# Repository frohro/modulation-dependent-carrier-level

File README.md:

# AWR MDCL Board
The YSE50 Amplitude Modulation Compandor (AMC) board for the ABB (ASEA Brown Bovari) SK-52 transmitters was redesigned  at AWR because we wanted a way to automatically reduce the transmitter power in real-time based on signal-to-noise ratio measurements in the target area.  It also provides us an opportunity to change the modulation-dependent carrier level (MDCL) automatically in real-time, based on the program content and/or the signal-to-noise ratio in the target area.  

This design should work with any transmitter using an ABB PSM (pulse step modulator) for AM or SW broadcasting designed in the 1980s or 1990s. It replaces the YSE 50 or YSE 21 PCBs in the PSM.  I suspect it should work with any transmitter using the YSE 21 or YSE 50.  These boards cost around \\$90,000 around the turn of the century, but you should be able to build this one for about $150 each in 2024, the most expensive parts are the DIN connectors that mate the board to the transmitter.  These boards are far better, because they use software to do the MDCL and facilitate experimentation and optimization.

## MDCL
Adventist World Radio (AWR) on Guam uses modulation-dependent carrier level (MDCL) which is a way of modifying the transmitted AM signal so it uses less power than standard amplitude modulation while hopefully not reducing the listenership.  AM was designed so receivers could be built easily and inexpensively using the technology available in the early 20th century.  A sinusoid at the radio frequency would be modulated (have its amplitude adjusted) as the desired audio signal, $m(t)$, went up and down.  If the radio frequency (RF) sine wave was $A cos(\omega_c t)$ and the audio signal to be transmitted was $m(t)$ where $|m(t)| < 1$, the transmitted signal, $v(t)$ is given by $A(1+m(t))cos(\omega_c t)$. Keeping the magnitude of the audio signal less than one makes $m(t)$ easy to remove from $v(t)$ with an envelope detector enabling very simple receivers to be constructed.  Unfortunately, there is no information in the $1$ term of $(1 + m(t))$, but it does take energy to send it.  If the audio is very soft so that $m(t) << 1$, and the goal is to transmit the information in $m(t)$, it seems especially wasteful.  (Note: Even a public address system playing an analog audio signal like $m(t)$ isn't an equal cost per bit of information.  Loud signals require more power, but they don't always contain more information.  Sometimes the quiet whisper of a friend is worth far more than the loud talk going on.  But for AM modulation the $1$ term has almost nothing to do with the $m(t)$, so it indeed seems a waste to send, at least in a certain sense.)

There are two different types of MDCL, Dynamic Carrier Control (DCC) and Amplitude Modulation Companding (AMC).  

### DCC
DCC reduces the $1$ term in $1 + m(t)$, so less carrier power is transmitted when less is needed, keeping the percentage modulation closer to 100% where the peaks of $m(t) = 1$.   The  DCC signal would be $v_{DCC}(t) = A(k(t)+m(t))cos(\omega_c t)$ .  Because the factor $k < 1$ DCC saves some energy that would have been sent in the carrier perhaps unnecessarily.  It is a slowly varying function of time compared to $m(t)$, so we often think of it as a constant, just $k$. Suppose $k$ was reduced to zero when $m(t) = 0$, then other interfering signals would likely be heard by the receiver instead of silence because most receivers have automatic gain control (AGC) which adjusts the gain up when the signal goes down.  To combat this, $k$ is not usually reduced all the way down to zero.  This leaves a flat carrier for silence, which is usually strong enough that the small noise will be masked out and the receiver will produce silence.

All MDCL schemes use a fast attack slow decay signal based on the absolute value of the modulation signal.  If $m(t)$ quickly gets louder, the changes we make to the RF signal need to respond quickly, but if $m(t)$ decreases in amplitude we should respond slowly to minimize artifacts of our signal processing.  So the first step in doing MDCL is to construct this signal.  We call this signal $m_p(t) = f(|m(t)|)$ where $f$ is the fast attack, slow decay function of time.  In the old analog days, a circuit like this where the capacitor is charged based on the $R_{attack} C$ time-constant and decays based on the $R_{decay} C$ time-constant.  (Rob, replace this figure when you get your tablet-PC going again.)

would have been used.

Below, you can see how $k$ is computed as a function of $m_p(t)$ for DCC.  This function is somewhat heuristic.  The one shown is used in the YSE21 board.  Sometimes $k$ goes back up for low values of $m_p(t)$ to help silence be silent in a real receiver in the presence of interference.

```python
import matplotlib.pyplot as plt
import numpy as np

# Define the x values
x = np.linspace(0, 1, 500)

# Define the y values based on the condition
y = np.piecewise(x, [x < 0.5, x >= 0.5], [0.5, lambda x: (x-0.5)+0.5])

# Create the plot
plt.plot(x, y)

# Label the axes
plt.xlabel('$m_p(t)$')
plt.ylabel('k')

# Set the range for the axes
plt.xlim(0, 1)
plt.ylim(0, 1)

plt.title('DCC Carrier Level, k')

# Display the plot
plt.show()
```

### AMC
AMC takes the view that the soft or silent portions of the broadcast are more important to preserve than the loud portions.  This may be more appropriate for music rather than talk.  It adjusts the amplitude of $v(t)$, instead of just the carrier, as a function of $m_p(t)$ so  $v_{AMC} = A (A_{REL}(1+m(t)))$.  The following graph shows $A_{REL}$ as a function of $m_p(t)$.  Note again, that makes $A_{REL}$ a function of $t$, but since it is relatively slowly varying compared with $m(t)$, so we just call it $A_{REL}$.  

```python
# Define the x values
x = np.linspace(0, 1, 500)

# Define the y values based on the condition
y = np.piecewise(x, [x < 0.1, x >= 0.1], [1, lambda x: (-0.5/.9*x+1+.1*.5/.9)])

# Create the plot
plt.plot(x, y)

# Label the axes
plt.xlabel('$m_p(t)$')
plt.ylabel('$A_{REL}$')

# Set the range for the axes
plt.xlim(0, 1)
plt.ylim(0, 1.1)

plt.title('AMC Relative Signal Level, $A_{REL}$')

# Display the plot
plt.show()
```

AMC peak output power of the transmitter is the same as the output from the carrier alone.  For example, an SK-52 transmitter with a normal AM power level specified at 100 kW, means the carrier alone will output 100 kW average power.  On peak modulation, the output will be 400 kW because the $m(t)$ adds to the $1$ to become $2$ for 100% modulation at peaks of $m(t)$ giving $4$ times the power because power is proportional to the square of the voltage which is twice what it was for the carrier alone.  AMC thus saves power and wear and tear on the transmitter, by reducing the average power it is transmitting under larger modulation.  

There are variations on these two themes of MDCL one can dream about.  It is claimed that AMC is better for music, while DCC is better for speech.  AMC is more popular with medium wave AM stations.  It may sound better at least to some.  DCC only reduces carrier power, and that really doesn't contain any information other than silence.  Previous experiments with DCC indicated it actually sounds louder to the listener due to the way the receiver AGC and the transmitter DCC interact which is good for short wave.  AMC will save the station more money than DCC, but so would simply turning the power down.  Turning the power down is the major improvement we wish to add to the options, so we can use AMC, DCC, or ordinary AM, but only the power needed.  In the past it was not easy to measure how much power was needed, but now with Internet connected receivers, it can be done fairly easily.  Since the space weather changes the signal levels for skywave signals, this will change over time, so there will be times when less power is needed than the maximum possible.  In general a cut in power by half is only barely perceptible to the listener, so significant savings on the power bill can be expected.  The plan is to measure the signal-to-noise ratio every 15 minutes or so and change the transmitter power as appropriate.

## Transmitter Operation
AWR Guam has five ABB SK-52 100 kW transmitters.  They use the standard modulation method, where the B+ high voltage on the plate of the final amplifiers is supplied by the modulator, which produces an amplified version of the output of the MDCL output signal.  By varying this voltage on the plate of the final RF amplifier, the output signal’s amplitude is set.  This is called modulating the transmitter.   See the diagram below.

A Pulse Step Modulator (PSM) is used to create the “Audio + DC Carrier Voltage” in the diagram above.  The PSM is essentially like a digital to analog converter where 26 voltage sources are switched in series by digital signals.  It is like a 26 level digital to analog converter with an output of 22 kV maximum.  When the AM transmitter (no MDCL) is sending silence, the PSM puts out 11 kV.  At 100% modulation where the $max (|m(t)|) = 1$, it puts out between 0 and 22 kV as the audio, $m(t)$ goes up and down.  Below is a basic diagram of a PSM.  The switches are controlled digitally and in the SK-52 are gate turn off (GTO) devices.  The blue, green, magenta and orange circular symbols are voltage sources.  (Rob, to avoid copyright, we could replace these when you have your bricked computer back.)

The most obvious place in the circuit to incorporate a modification to the SK-52 transmitters is in the MDCL board, so YS50 was replaced.  The MDCL board is where something can be incorporated into the circuit to lower the power when a remote Internet connected receiver in the target area indicates the transmitter could cut power without significantly lowering the number of listeners.  We just add one more parameter we can control that multiplies whatever type of audio signal we have by a slowly varying "constant", that changes perhaps every 15 minutes as the signal-to-noise ratio is updated.  If this constant is called $A_{att}$, it would have a maximum value of $1$ for maximum power, and $0.707$ for half power, or $0.5$ for quarter power.  

Note in the blue AM Transmitter Block Diagram above, the screen grid in the vacuum tube.  Unless the voltage on the screen is also controlled by the MDCL board, a risk exists that the screen current will increase beyond acceptable limits.  For example if the plate of the tube is at $0$ volts, and the screen at a higher voltage, the screen will act as the plate normally would and the screen current would be way to high.  This means there is a limit to how much we can drop $A_{att}$.  A solution to this problem is to increase the resistor between the screen supply and the screen.  We were able to drop the power to 25% of maximum.  (Rob, make sure this is correct.)

We also noted a problem with the PSM protection circuitry which styll needs to be ironed out.

The transmitter has a limit to how long the modulation, $m(t)$ can exceed a certain value, so that the transmitter is not operated beyond 100 kW for longer than is good for it.  This limit is enforced in the MDCL software as well.

## Board Description

### Hardware
The hardware is based on a [PJRC Teensy 4.1 development board](https://www.pjrc.com/store/teensy41.html).  It features a 600 MHz ARM Cortex-M7 processor with FPU, nice Arduino DSP library, a USB 2.0 port and Ethernet.  The data $1+m(t)$ comes in as a 5V TTL digital 12-bit parallel signal sampled at 100 kHz.  This signal is converted to a serial signal by a pair of 74LV165 parallel to serial conversion ICs.  These also convert the 5V TTL level signals of the input data to 3.3 V logic levels.  This serial data is read into the Teensy using SPI0.  The Teensy processes the signal as needed and sends the data to a serial to parallel conversion performed by a pair of 74ACHT595 ICs, which send the result on to the next board in the transmitter.  There is a CH340G that allows use of a second USB serial port for debugging (Serial2 for the Arduino) and four connectors for the inexpensive eight bit logic analyzers from China to read the serial and parallel data.  There are a number of LEDs for indicators and debugging and some provision for connecting other signals to the Teensy in case we overlooked something.  The Teensy we are using comes with Ethernet, and we send the real-time control signals over that medium.

The Teensy has a feature that may eventually be used to eliminate the analog stages of the whole broadcast system, making the whole system at KSDA digital, from the digital audio in all the way to the PSM of the transmitter.  This feature is the USB connector on the Teensy can be made to look just like a USB sound card for a computer operating at the 44.1 kHz sample rate. I have tested the Linux sample rate conversion library runing a sinc interpolator and it looks feasible to convert from 44.1 kHz to 100 kHz in real time, leaving about half the time between 100 kHz samples for DSP.  Optical USB extenders can be used to span the distance between the transmitters and the audio distribution computer.

### Software

#### Toolchain
You can build this with the Arduino IDE using Teensyduino or with VScode.  The latter gives you a nicer environment, but the former is quicker to set up.

#### Serial Input
The SPI (SPI0) is used for the serial data transfer of the input data.  The upper four bits of the 16 bit word should be zero.  If not, you have RFI or something bad happening.  The Teensy 4.1 supports a depreciated legacy way or doing the transactions, but also has the new recommend way.  Using that method, the speed can be increased from 12 MHz to 80 MHz.  The setup function shows how to set things up, and the ISR is shown below:
// ISR function called by the interrupt that is triggered by L1
// to process the new word from the transmitter
void receive2ByteWord() // Receive 16-bit word from SPI0
{                       // Select the slave device
  SPI.beginTransaction(spiSettings);
  digitalWrite(chipSelectPin0, LOW);
  // Send a dummy byte to initiate the SPI read and receive the 16-bit word
  uint16_t dummy = 0x00;
  receivedWord = SPI.transfer16(dummy); // Deselect the slave device
  digitalWrite(chipSelectPin0, HIGH);
  validWord = 1; // Indicates that the new 16-bit word is received and ready to process
  SPI.endTransaction();
}
#### Serial Output
The SPI1 bus is used for transferring data to the serial to parallel converter so the data will be ready for a parallel read by the transmitter.  Like the serial input, the setup function gets the SPI initialized and the following code is the ISR that happens when triggered by LC.
// ISR function called by the interrupt that is triggered by L5 to send the
// processed word to the transmitter (DCC board used LC, but L5 is faster)
void send2ByteWord()
{
  SPI1.beginTransaction(spiSettings);

  digitalWrite(chipSelectPin1, LOW); //  We are not using CS1.
  SPI1.transfer16(wordToSend);       // Send the 16-bit word to the transmitter
  digitalWrite(chipSelectPin1, HIGH);
  SPI1.endTransaction();
}
DCC and MDCL Processing
uint16_t processMDCL(uint16_t one_plus_m_t)
// See the MDCL.ipynb for the theory on this.
{ // This function takes a 16-bit word whose lower 12 bits is 1+m(t) and processes it according to the MDCL algorithm
  // We could put a check for overmodulation here if wanted (Check for repeated 0's)
  if (digitalRead(SSBOnOffPin) == LOW && digitalRead(NFBereitPin) == HIGH && digitalRead(DCCOnOffPin) == HIGH)
  { // if MCDL is on
    uint16_t m_p;
    static uint16_t m_pPrevious = 0;     // store the previous m_p(t) value
    static uint16_t samplesUntilDecay = samplesPerDecay; // This is the number of samples until the decay starts

    if (one_plus_m_t < 2048)           // Find |m(t)| value where 1 + m(t) scaled to 0 to 4095
    {
      m_p = 2048 - one_plus_m_t; // This should not overflow.
    }
    else
    {
      m_p = one_plus_m_t - 2048; // This should not overflow.
    }
    #ifdef DEBUG
    uint16_t m_p_a;
    m_p_a = m_p;  // mpa is for debugging.  It is m_p without the decay.
    #endif
    // m_p(t) needs to be a fast attack, slow decay function of time
    if (m_p <= m_pPrevious) // m_p is decreasing
    { 
      m_p = m_pPrevious; // m_p(t) should not decrease
      if (samplesUntilDecay > 0) // Will decay down to close to 0 (within samplesPerDecay) if m_p(t) is not increasing
      {
        samplesUntilDecay--;
      }
      else // sammples until decay is 0, so decay one step
      {
        if (m_p > 0) m_p--; // m_p should not be decreased below zero
        samplesUntilDecay = samplesPerDecay; // Reset the decay counter
      }
    }
    else // m_p in increasing so don't decay m_p(t).  It needs to rise instantly, but samplesPerDecay needs to be reset so it is ready for the next decay.
    {
      samplesUntilDecay = samplesPerDecay; // Reset the decay counter
    }
    m_pPrevious = m_p; // Store the current m_p(t) value for the next cycle
    if (currentMDCLNumber == 0) // DCC
    {
      if (digitalRead(DCCPin) != HIGH) // Change indicator LEDs if needed
      {
        digitalWrite(DCCPin, HIGH);
        digitalWrite(AMCPin, LOW);
      }
      uint16_t dccK; // See the graph of DCC k as a function of m_p(t).  We may want to pass the 430 and 1024 parameters in someday
      if (m_p > 1024)
      {
        dccK = m_p;
      }
      else if (m_p < 430) // Using curve as used for ABB high power transmitters (> 100 kW)
      {
        dccK = 1454 - m_p;  // 1454 = 1024 + 430
      }
      else
      {
        dccK = 1024;
      }
      return percentAdjust * ((dccK + one_plus_m_t)-2048); // percentAdjust is to turn the power down
    }
    else if (currentMDCLNumber == 1) // AMC
    {
      if (digitalRead(AMCPin) != HIGH) // Change the indicator LEDs if needed
      {
        digitalWrite(DCCPin, LOW);
        digitalWrite(AMCPin, HIGH);
      }
      {
        digitalWrite(DCCPin, LOW);
        digitalWrite(AMCPin, HIGH);
      }
      float AMC_REL = (2048 - m_p / 2)/2048.0;                        // This should not overflow.
      return percentAdjust * ((AMC_REL * one_plus_m_t)); // percentAdjust < 1, is to turn the power down
    }
  }
  return percentAdjust * one_plus_m_t; // If MDCL is off, just pass the word through adjusted for desired power output
}

#### Keeping from Damaging the Transmitter by Asking for Too Much Power
The PSM manual description of YSE27 (pages 42-44) describe how long a signal that would transmit more than 100 kW is allowed.  You cannot have more than 2500 for longer than 10 mS.  If it happens, then you need to drop to the carrier level (2048) until the signal goes below the carrier level.  At first I was unable to determine if YSE27 was before or after YSE21 (the DCC unit we are replacing) so we wrote a safety routine that kept the MDCL board from violating the conditions needed for a healthy transmitter described there.  There were still possibilities of a bug that this would not catch, so I went back and finally found that YSE21 is before YSE27 in the transmitter.  It makes more sense to put this check at the end of the line, not in the DCC section, so our code was redundant, and was a possible place for bugs.  The block diagram in section 5 of Volume 7 Schematic Diagrams AF Stages (PSM), YSE-27 documents this.  I am removing our redundant code to make the software simpler.  (Rob 9/2/24).  This relieves a fear that we could ask the transmitter for more power than it could handle and it would burn up.

#### Screen Modifications
The final tube screen voltage gets more and more attractive for electrons relative to the plate (anode) so an extra screen resistor was added to the screen power supply and possibly the voltage tap will be changed to reduce the screen voltage.

### Things Tested and Look Good
* SPI at 80 MHz both in and out good!
    * No data outside the 12 bit range like Ray had with the slower SPI
* Timing of SPI (input and output)
* Main loop usually happens every uS, but every 4th time it is 3.5 uS
* processMDCL with dontBurnTransmitterUP uses 300 nS (0.3 uS)  (fast enough)
* MDCL works (tested using triangle under all conditions)
* Make sure if loop() is delayed, it just keeps sending out the same wordToSend.  This will cover short timing problems, where loop() gets delayed.  It does.  
* Watch out for RFI!
### Things to test
* Different MDCL types and power levels while listening to remote receivers
* Lower voltage taps on screen power supply
### Things to Improve
* The messages in TCP/IP communication are too long.
* The code quoted in this keeps improving, making this difficult to keep up to date.  We need a better way of documenting it.
### Priorities for Rob before leaving Guam in order of Priority
* Get the MDCL board running smoothly.  Hopefully we can be running it in one of the transmitters full time by the time I leave.
    * Investigate how different MDCL methods and power levels are seen from remote receivers.
    * Documentation for the MDCL board and videos
* Finish getting the PostgreSQL database going for automated monitoring.
* Get the automated power level software going.

## Operation
#### RFI
Beware of RFI.  The PSM in the transmitter gets ">OFF" errors (meaning it is taking too long to turn off PSM modules, which is bad because the switch (GTO) dissipates power whenever it is turning on or off and the energy dissipated depends on how quickly you switch).  These appear to be caused by RF feedback into the system through the MDCL board when it is on the extender board for testing.  So only test it with it inside the transmitter case if the test involves transmitting, and do not leave any cables connected to it because they act as antennas.  If cables must be connected, use ferrite torroids to suppress common mode RF and optical fiber instead of copper wires wherever possible.

Compute what the minimum power output will be with your MDCL and make sure it does not go below 10 kW.  We could put a test in the code to not send something below 648.

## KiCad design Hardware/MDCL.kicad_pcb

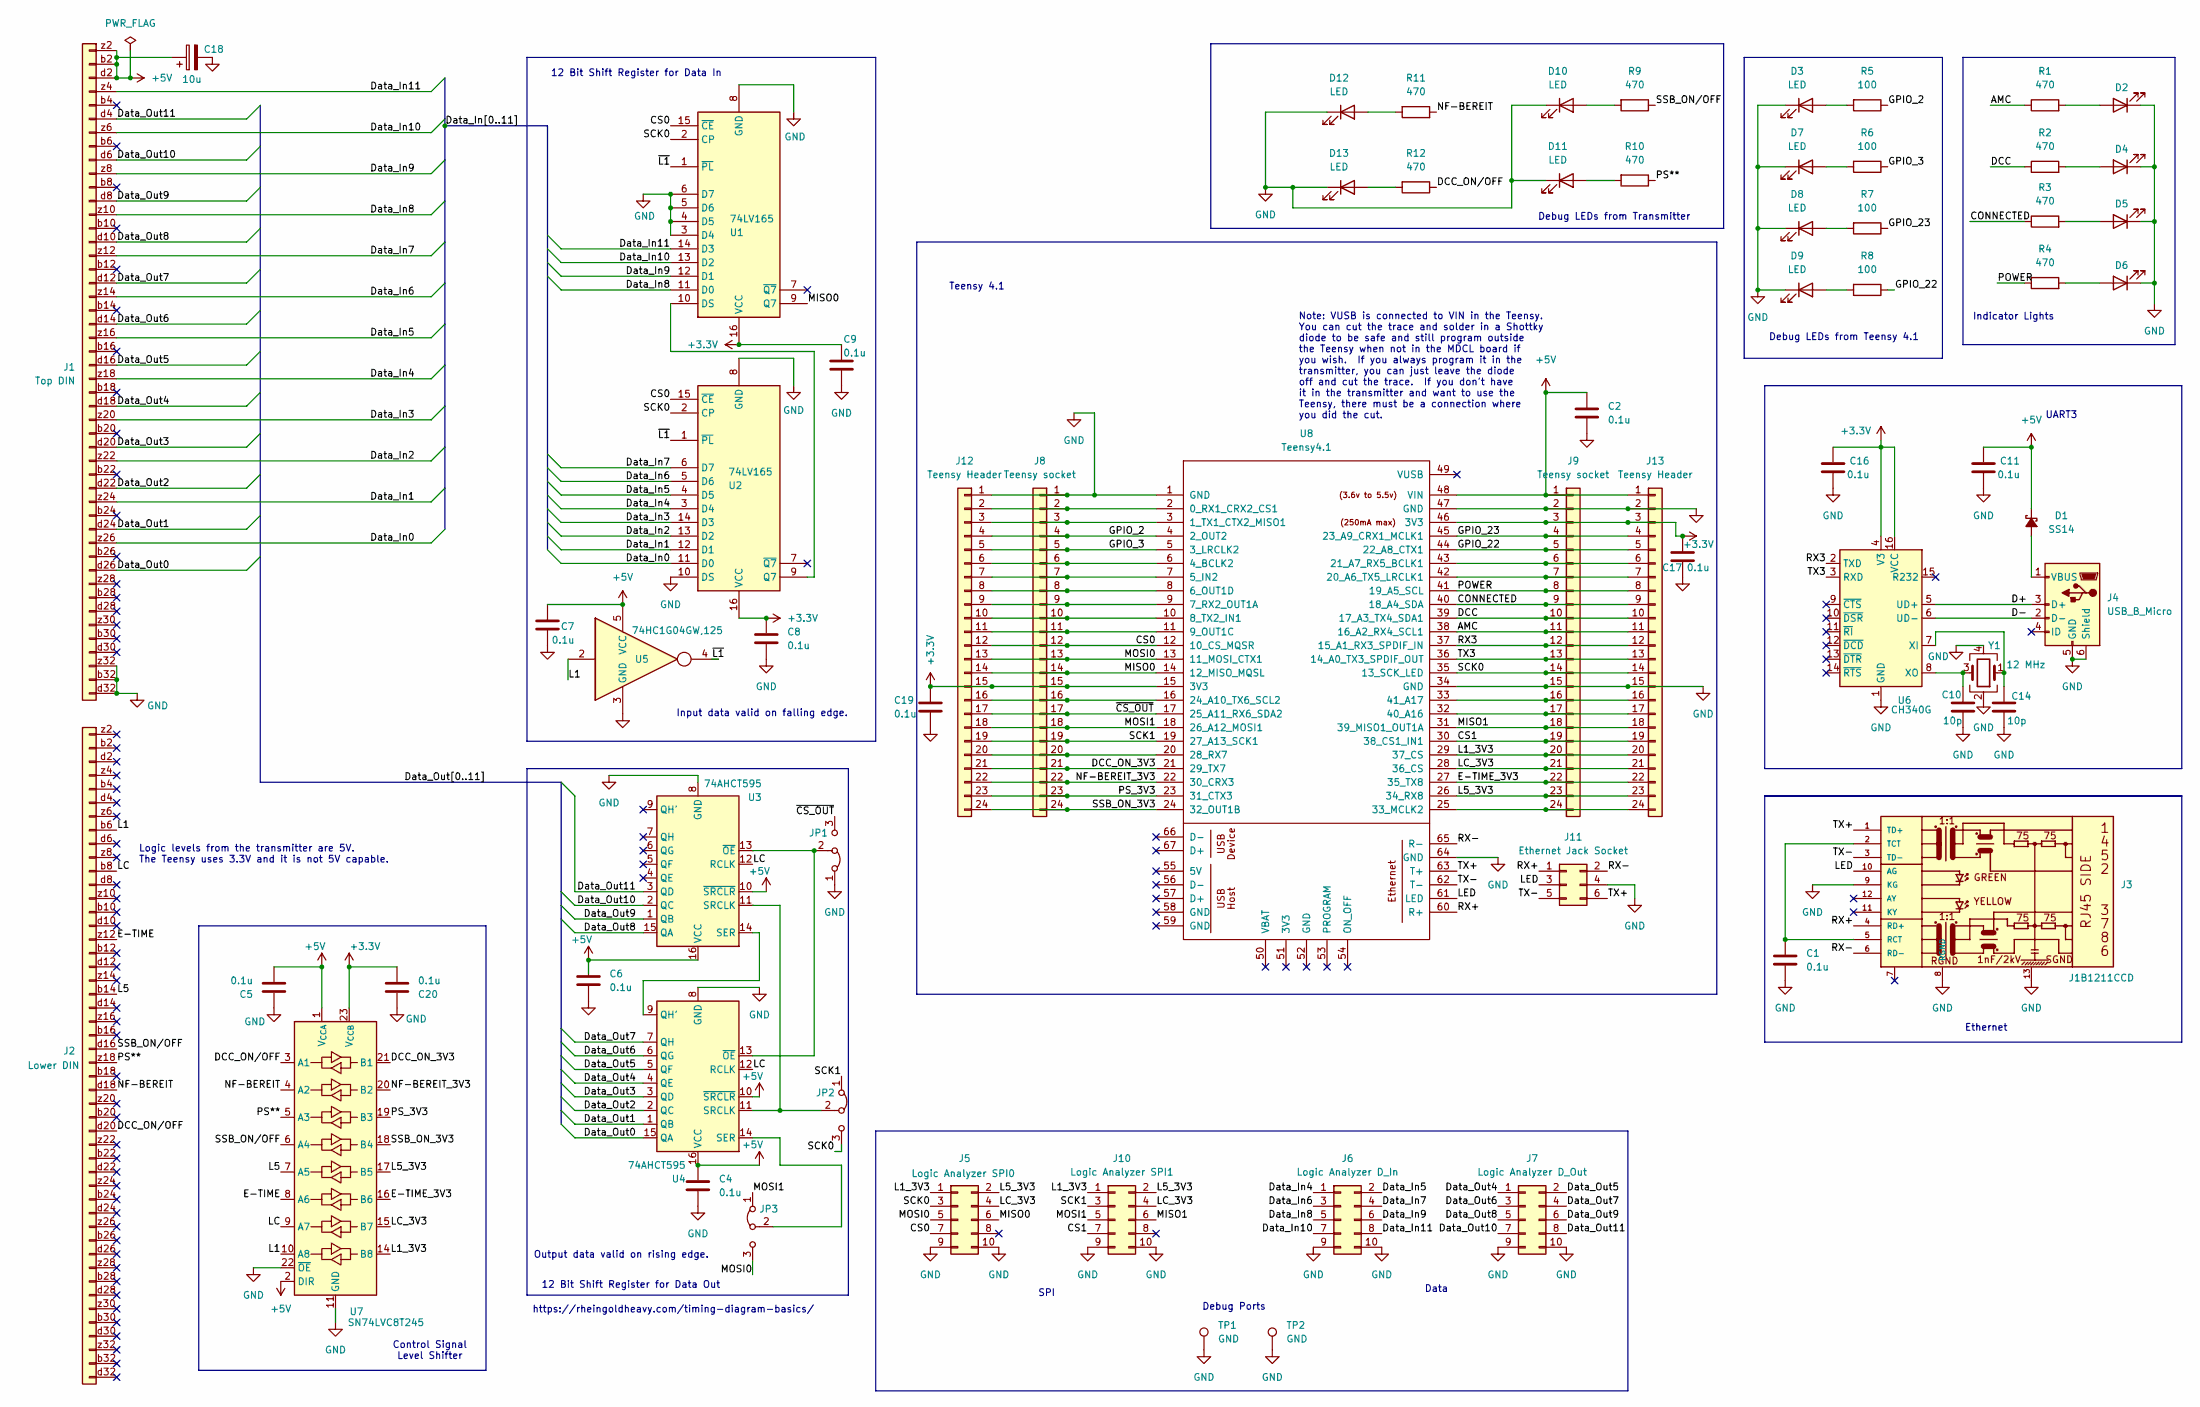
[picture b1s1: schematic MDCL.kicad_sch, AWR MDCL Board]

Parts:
C1, C2, C4, C5, C6, C7, C8, C9, C11, C16, C17, C19, C20: 0.1u; C_0805_2012Metric; LCSC C49678
C10, C14: 10p; C_0603_1608Metric; LCSC C1634
C18: 10u; C_0805_2012Metric; LCSC C15850
D1: SS14; D_SMA; LCSC C2480
D2, D4, D5, D6: HV-32H307B/260/XSYG; LED_3.0mm_2.54mm_lead_spacing_horizontal
D3, D7, D8, D9, D10, D11, D12, D13: LED; LED_0603_1608Metric; LCSC C2290
J1: Top DIN; DIN41612_F_3x16_Male_Horizontal_THT
J2: Lower DIN; DIN41612_F_3x16_Male_Horizontal_THT
J3: J1B1211CCD; RJ45_Cetus_J1B1211CCD_Horizontal; LCSC C910371
J4: USB_B_Micro; USB_Micro-Yuandi-G3P3-A1T2; LCSC C2682512
J5: Logic Analyzer SPI0; IDC-Header_2x05_P2.54mm_Vertical_SMD; LCSC C2843214
J6: Logic Analyzer D_In; IDC-Header_2x05_P2.54mm_Vertical_SMD; LCSC C2843214
J7: Logic Analyzer D_Out; IDC-Header_2x05_P2.54mm_Vertical_SMD; LCSC C2843214
J8, J9: Teensy socket; PinHeader_1x24_P2.54mm_Vertical; LCSC C7506622
J10: Logic Analyzer SPI1; IDC-Header_2x05_P2.54mm_Vertical_SMD; LCSC C2843214
J11: Ethernet Jack Socket; PinHeader_2x03_P2.00mm_Vertical_SMD; LCSC C3975167
J12, J13: Teensy Header; PinHeader_1x24_P2.54mm_Vertical
JP1, JP2, JP3: Jumper_3_Bridged12; SolderJumper-3_P1.3mm_Bridged12_RoundedPad1.0x1.5mm_NumberL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
R1, R2, R3, R4: 470; R_1206_3216Metric; LCSC C17936
R5, R6, R7, R8: 100; R_0805_2012Metric; LCSC C17408
R9, R10, R11, R12: 470; R_0603_1608Metric; LCSC C23179
TP1, TP2: GND; TestPoint_THTPad_4.0x4.0mm_Drill2.0mm
U1, U2: 74LV165; TSSOP-16_4.4x5mm_P0.65mm; LCSC C201716
U3, U4: 74AHCT595; TSSOP-16_4.4x5mm_P0.65mm; LCSC C554707
U5: 74HC1G04GW,125; SOT-353_SC-70-5; LCSC C10234
U6: CH340G; SOP-16_3.9x9.9mm_P1.27mm; LCSC C14267
U7: SN74LVC8T245; TSSOP-24_4.4x7.8mm_P0.65mm; LCSC C7859
U8: Teensy4.1
Y1: 12 MHz; Crystal_SMD_2520-4Pin_2.5x2.0mm; LCSC C963522

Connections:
+3.3V: C8.1, C9.1, C16.1, C17.1, C19.1, C20.2, J8.15, J9.3, J12.15, J13.3, U1.16 (VCC), U2.16 (VCC), U6.4 (V3), U6.16 (VCC), U7.23 (V_{CCB}), U7.24 (V_{CCB}), U8.15 (3V3), U8.46 (3V3)
+5V: C2.1, C4.1, C5.2, C6.1, C7.1, C11.1, C18.1, D1.1 (K), J1.b2, J1.d2, J1.z2, J9.1, J13.1, U3.10 (~SRCLR), U3.16 (VCC), U4.10 (~SRCLR), U4.16 (VCC), U5.5 (VCC), U7.1 (V_{CCA}), U7.2 (DIR), U8.48 (VIN)
/AMC: J9.11, J13.11, R1.1, U8.38 (16_A2_RX4_SCL1)
/CONNECTED: J9.9, J13.9, R3.1, U8.40 (18_A4_SDA)
/CS0: J5.7, J8.12, J12.12, U1.15 (~CE), U2.15 (~CE), U8.12 (10_CS_MQSR)
/CS1: J9.19, J10.7, J13.19, U8.30 (38_CS1_IN1)
/D+: J4.3 (D+), U6.5 (UD+)
/D-: J4.2 (D-), U6.6 (UD-)
/DCC: J9.10, J13.10, R2.1, U8.39 (17_A3_TX4_SDA1)
/DCC_ON_3V3: J8.21, J12.21, U7.21 (B1), U8.21 (29_TX7)
/DCC_ON/OFF: J2.d20, R12.1, U7.3 (A1)
/Data_In0: J1.z26, U2.11 (D0)
/Data_In1: J1.z24, U2.12 (D1)
/Data_In2: J1.z22, U2.13 (D2)
/Data_In3: J1.z20, U2.14 (D3)
/Data_In4: J1.z18, J6.1, U2.3 (D4)
/Data_In5: J1.z16, J6.2, U2.4 (D5)
/Data_In6: J1.z14, J6.3, U2.5 (D6)
/Data_In7: J1.z12, J6.4, U2.6 (D7)
/Data_In8: J1.z10, J6.5, U1.11 (D0)
/Data_In9: J1.z8, J6.6, U1.12 (D1)
/Data_In10: J1.z6, J6.7, U1.13 (D2)
/Data_In11: J1.z4, J6.8, U1.14 (D3)
/Data_Out0: J1.d26, U4.15 (QA)
/Data_Out1: J1.d24, U4.1 (QB)
/Data_Out2: J1.d22, U4.2 (QC)
/Data_Out3: J1.d20, U4.3 (QD)
/Data_Out4: J1.d18, J7.1, U4.4 (QE)
/Data_Out5: J1.d16, J7.2, U4.5 (QF)
/Data_Out6: J1.d14, J7.3, U4.6 (QG)
/Data_Out7: J1.d12, J7.4, U4.7 (QH)
/Data_Out8: J1.d10, J7.5, U3.15 (QA)
/Data_Out9: J1.d8, J7.6, U3.1 (QB)
/Data_Out10: J1.d6, J7.7, U3.2 (QC)
/Data_Out11: J1.d4, J7.8, U3.3 (QD)
/E-TIME: J2.z12, U7.8 (A6)
/E-TIME_3V3: J9.22, J13.22, U7.16 (B6), U8.27 (35_TX8)
/GPIO_2: J8.4, J12.4, R5.1, U8.4 (2_OUT2)
/GPIO_3: J8.5, J12.5, R6.1, U8.5 (3_LRCLK2)
/GPIO_22: J9.5, J13.5, R8.1, U8.44 (22_A8_CTX1)
/GPIO_23: J9.4, J13.4, R7.1, U8.45 (23_A9_CRX1_MCLK1)
/L1: J2.b6, U5.2, U7.10 (A8)
/L1_3V3: J5.1, J9.20, J10.1, J13.20, U7.14 (B8), U8.29 (37_CS)
/L5: J2.b14, U7.7 (A5)
/L5_3V3: J5.2, J9.23, J10.2, J13.23, U7.17 (B5), U8.26 (34_RX8)
/LC: J2.b8, U3.12 (RCLK), U4.12 (RCLK), U7.9 (A7)
/LC_3V3: J5.4, J9.21, J10.4, J13.21, U7.15 (B7), U8.28 (36_CS)
/LED: J3.10 (AG), J11.3, U8.61 (LED)
/MISO0: J5.6, J8.14, J12.14, U1.9 (Q7), U8.14 (12_MISO_MQSL)
/MISO1: J9.18, J10.6, J13.18, U8.31 (39_MISO1_OUT1A)
/MOSI0: J5.5, J8.13, J12.13, JP3.3 (B), U8.13 (11_MOSI_CTX1)
/MOSI1: J8.18, J10.5, J12.18, JP3.1 (A), U8.18 (26_A12_MOSI1)
/NF-BEREIT: J2.d18, R11.1, U7.4 (A2)
/NF-BEREIT_3V3: J8.22, J12.22, U7.20 (B2), U8.22 (30_CRX3)
/POWER: J9.8, J13.8, R4.1, U8.41 (19_A5_SCL)
/PS**: J2.z18, R10.1, U7.5 (A3)
/PS_3V3: J8.23, J12.23, U7.19 (B3), U8.23 (31_CTX3)
/RX3: J9.12, J13.12, U6.2 (TXD), U8.37 (15_A1_RX3_SPDIF_IN)
/RX+: J3.4 (RD+), J11.1, U8.60 (R+)
/RX-: J3.6 (RD-), J11.2, U8.65 (R-)
/SCK0: J5.3, J9.14, J13.14, JP2.3 (B), U1.2 (CP), U2.2 (CP), U8.35 (13_SCK_LED)
/SCK1: J8.19, J10.3, J12.19, JP2.1 (A), U8.19 (27_A13_SCK1)
/SSB_ON_3V3: J8.24, J12.24, U7.18 (B4), U8.24 (32_OUT1B)
/SSB_ON/OFF: J2.d16, R9.1, U7.6 (A4)
/TX3: J9.13, J13.13, U6.3 (RXD), U8.36 (14_A0_TX3_SPDIF_OUT)
/TX+: J3.1 (TD+), J11.6, U8.63 (T+)
/TX-: J3.3 (TD-), J11.5, U8.62 (T-)
/~CS_OUT: J8.17, J12.17, JP1.3 (B), U8.17 (25_A11_RX6_SDA2)
/~L1: U1.1 (~PL), U2.1 (~PL), U5.4
GND: C1.2, C2.2, C4.2, C5.1, C6.2, C7.2, C8.2, C9.2, C10.2, C11.2, C14.2, C16.2, C17.2, C18.2, C19.2, C20.1, D2.2 (K), D3.1 (K), D4.2 (K), D5.2 (K), D6.2 (K), D7.1 (K), D8.1 (K), D9.1 (K), D10.1 (K), D11.1 (K), D12.1 (K), D13.1 (K), J1.b32, J1.d32, J1.z32, J3.8 (RGND), J3.9 (KG), J3.13, J4.5 (GND), J4.6 (Shield), J5.9, J5.10, J6.9, J6.10, J7.9, J7.10, J8.1, J9.2, J9.15, J10.9, J10.10, J11.4, J12.1, J13.2, J13.15, JP1.1 (A), TP1.1, TP2.1, U1.3 (D4), U1.4 (D5), U1.5 (D6), U1.6 (D7), U1.8 (GND), U2.8 (GND), U2.10 (DS), U3.8 (GND), U4.8 (GND), U5.3 (GND), U6.1 (GND), U7.11 (GND), U7.12 (GND), U7.13 (GND), U7.22 (~OE), U8.1 (GND), U8.34 (GND), U8.47 (GND), U8.64 (GND), Y1.2, Y1.4
unnamed: D1.2 (A), J4.1 (VBUS)
unnamed: D2.1 (A), R1.2
unnamed: D3.2 (A), R5.2
unnamed: D4.1 (A), R2.2
unnamed: D5.1 (A), R3.2
unnamed: D6.1 (A), R4.2
unnamed: D7.2 (A), R6.2
unnamed: D8.2 (A), R7.2
unnamed: D9.2 (A), R8.2
unnamed: D10.2 (A), R9.2
unnamed: D11.2 (A), R10.2
unnamed: D12.2 (A), R11.2
unnamed: D13.2 (A), R12.2
unnamed: C1.1, J3.2 (TCT), J3.5 (RCT)
unnamed: J8.2, J12.2, U8.2 (0_RX1_CRX2_CS1)
unnamed: J8.3, J12.3, U8.3 (1_TX1_CTX2_MISO1)
unnamed: J8.6, J12.6, U8.6 (4_BCLK2)
unnamed: J8.7, J12.7, U8.7 (5_IN2)
unnamed: J8.8, J12.8, U8.8 (6_OUT1D)
unnamed: J8.9, J12.9, U8.9 (7_RX2_OUT1A)
unnamed: J8.10, J12.10, U8.10 (8_TX2_IN1)
unnamed: J8.11, J12.11, U8.11 (9_OUT1C)
unnamed: J8.16, J12.16, U8.16 (24_A10_TX6_SCL2)
unnamed: J8.20, J12.20, U8.20 (28_RX7)
unnamed: J9.6, J13.6, U8.43 (21_A7_RX5_BCLK1)
unnamed: J9.7, J13.7, U8.42 (20_A6_TX5_LRCLK1)
unnamed: J9.16, J13.16, U8.33 (41_A17)
unnamed: J9.17, J13.17, U8.32 (40_A16)
unnamed: J9.24, J13.24, U8.25 (33_MCLK2)
unnamed: JP1.2 (C), U3.13 (~OE), U4.13 (~OE)
unnamed: JP2.2 (C), U3.11 (SRCLK), U4.11 (SRCLK)
unnamed: JP3.2 (C), U4.14 (SER)
unnamed: U1.10 (DS), U2.9 (Q7)
unnamed: U3.14 (SER), U4.9 (QH')
unnamed: C14.1, U6.7 (XI), Y1.1
unnamed: C10.1, U6.8 (XO), Y1.3

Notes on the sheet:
Debug Ports
12 Bit Shift Register for Data In
Input data valid on falling edge.
https://rheingoldheavy.com/timing-diagram-basics/
Control Signal Level Shifter
UART3
Indicator Lights
Debug LEDs from Transmitter
Logic levels from the transmitter are 5V. The Teensy uses 3.3V and it is not 5V capable.
Ethernet
Data
Output data valid on rising edge.
12 Bit Shift Register for Data Out
Note: VUSB is connected to VIN in the Teensy. You can cut the trace and solder in a Shottky diode to be safe and still program outside the Teensy when not in the MDCL board if you wish. If you always program it in the transmitter, you can just leave the diode off and cut the trace. If you don't hav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
Teensy 4.1
SPI
Debug LEDs from Teensy 4.1

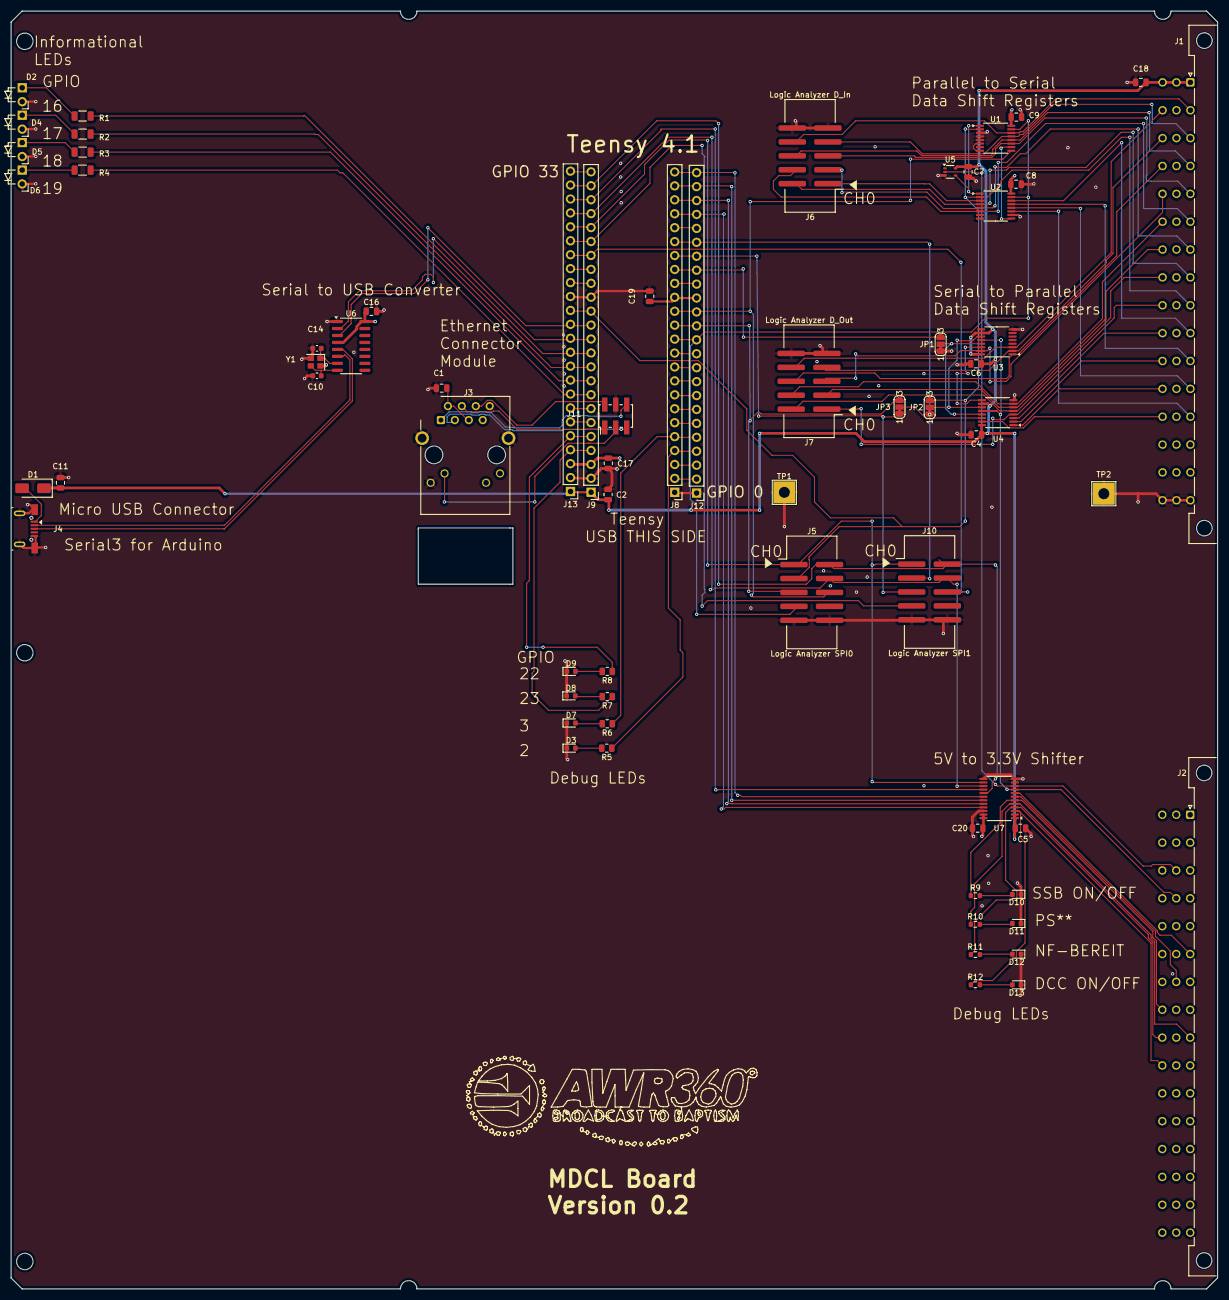
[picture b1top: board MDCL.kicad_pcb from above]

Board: 4 copper layers, 220.0 x 233.0 mm, 67 parts (0 on the bottom side), 106 nets.

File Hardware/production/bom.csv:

Designator,Footprint,Quantity,Value,LCSC Part #
"C1, C11, C16, C17, C19, C2, C20, C4, C5, C6, C7, C8, C9",0805,13,0.1u,C49678
"C10, C14",0603,2,10p,C1634
C18,0805,1,10u,C15850
D1,D_SMA,1,SS14,C2480
"D10, D11, D12, D13, D3, D7, D8, D9",0603,8,LED,C2290
"D2, D4, D5, D6",LED_3.0mm_2.54mm_lead_spacing_horizontal,4,HV-32H307B/260/XSYG,
J1,DIN41612_F_3x16_Male_Horizontal_THT,1,Top DIN,
J10,IDC-Header_2x05_P2.54mm_Vertical_SMD,1,Logic Analyzer SPI1,C2843214
J11,PinHeader_2x03_P2.00mm_Vertical_SMD,1,Ethernet Jack Socket,C3975167
J2,DIN41612_F_3x16_Male_Horizontal_THT,1,Lower DIN,
J3,RJ45_Cetus_J1B1211CCD_Horizontal,1,J1B1211CCD,C910371
J4,USB_Micro-Yuandi-G3P3-A1T2,1,USB_B_Micro,C2682512
J5,IDC-Header_2x05_P2.54mm_Vertical_SMD,1,Logic Analyzer SPI0,C2843214
J6,IDC-Header_2x05_P2.54mm_Vertical_SMD,1,Logic Analyzer D_In,C2843214
J7,IDC-Header_2x05_P2.54mm_Vertical_SMD,1,Logic Analyzer D_Out,C2843214
"J8, J9",PinHeader_1x24_P2.54mm_Vertical,2,Teensy socket,C7506622
"R1, R2, R3, R4",1206,4,75,C17888
"R10, R11, R12, R9",0603,4,470,C23179
"R5, R6, R7, R8",0805,4,100,C17408
"TP1, TP2",TestPoint_THTPad_4.0x4.0mm_Drill2.0mm,2,GND,
"U1, U2",TSSOP-16_4.4x5mm_P0.65mm,2,74LV165,C201716
"U3, U4",TSSOP-16_4.4x5mm_P0.65mm,2,74AHCT595,C554707
U5,SOT-353_SC-70-5,1,"74HC1G04GW,125",C10234
U6,SOP-16_3.9x9.9mm_P1.27mm,1,CH340G,C14267
U7,TSSOP-24_4.4x7.8mm_P0.65mm,1,SN74LVC8T245,C7859
Y1,Crystal_SMD_2520-4Pin_2.5x2.0mm,1,12 MHz,C963522

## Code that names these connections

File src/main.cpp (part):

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const int SSBOnOffPin = 32;    // Chip select pin for SPI0
const int NFBereitPin = 30;    // Chip select pin for SPI0
const int DCCOnOffPin = 29;    // Chip select pin for SPI0
const int powerPin = 19;       // pin connected to LED to show that board has power
const int connectedPin = 18;   // pin to show connected with the server
const int AMCPin = 16;         // used to activate LED to show AMC is being used
const int DCCPin = 17;         // used to activate LED to show DCC is being used
const int L5Pin = 34;          // GPIO pin for L5, which indicates when the Teensy 4.1 can send data to the transmitter

SPISettings spiSettings(80000000, MSBFIRST, SPI_MODE0); // 30 MHz, MSB first, SPI mode 0
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uint16_t wordToSend;          // stores word when it is ready to be sent to the transmitter
int samplesPerDecay = 10;      // Out of 4095, how much decay is there per sample for the slow decay of m_p(t)  1 is way to fast!
int validWord = 0;            // indicates the 16 bit word is ready to process 0 = not valid, 1 = valid
int currentMDCLNumber = 1;    // 0 = dcc, 1 = amc, 2 = other
float percentAdjust = 1;                                         ;      // range of 0 to 1 ... used to adjust overall voltage or power output of transmitter.
uint16_t processedWord;

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
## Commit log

2024-09-08 Rename README.ipynb to README.md
2024-09-08 added README.ipynb
2024-09-08 Rename README.md back to README.ipynb
2024-09-08 Convert README.ipynb to README.md
2024-09-08 Trying to make images appear in README.md
2024-09-26 Added Kicad files
2024-12-05 Fixed an equation in the README
